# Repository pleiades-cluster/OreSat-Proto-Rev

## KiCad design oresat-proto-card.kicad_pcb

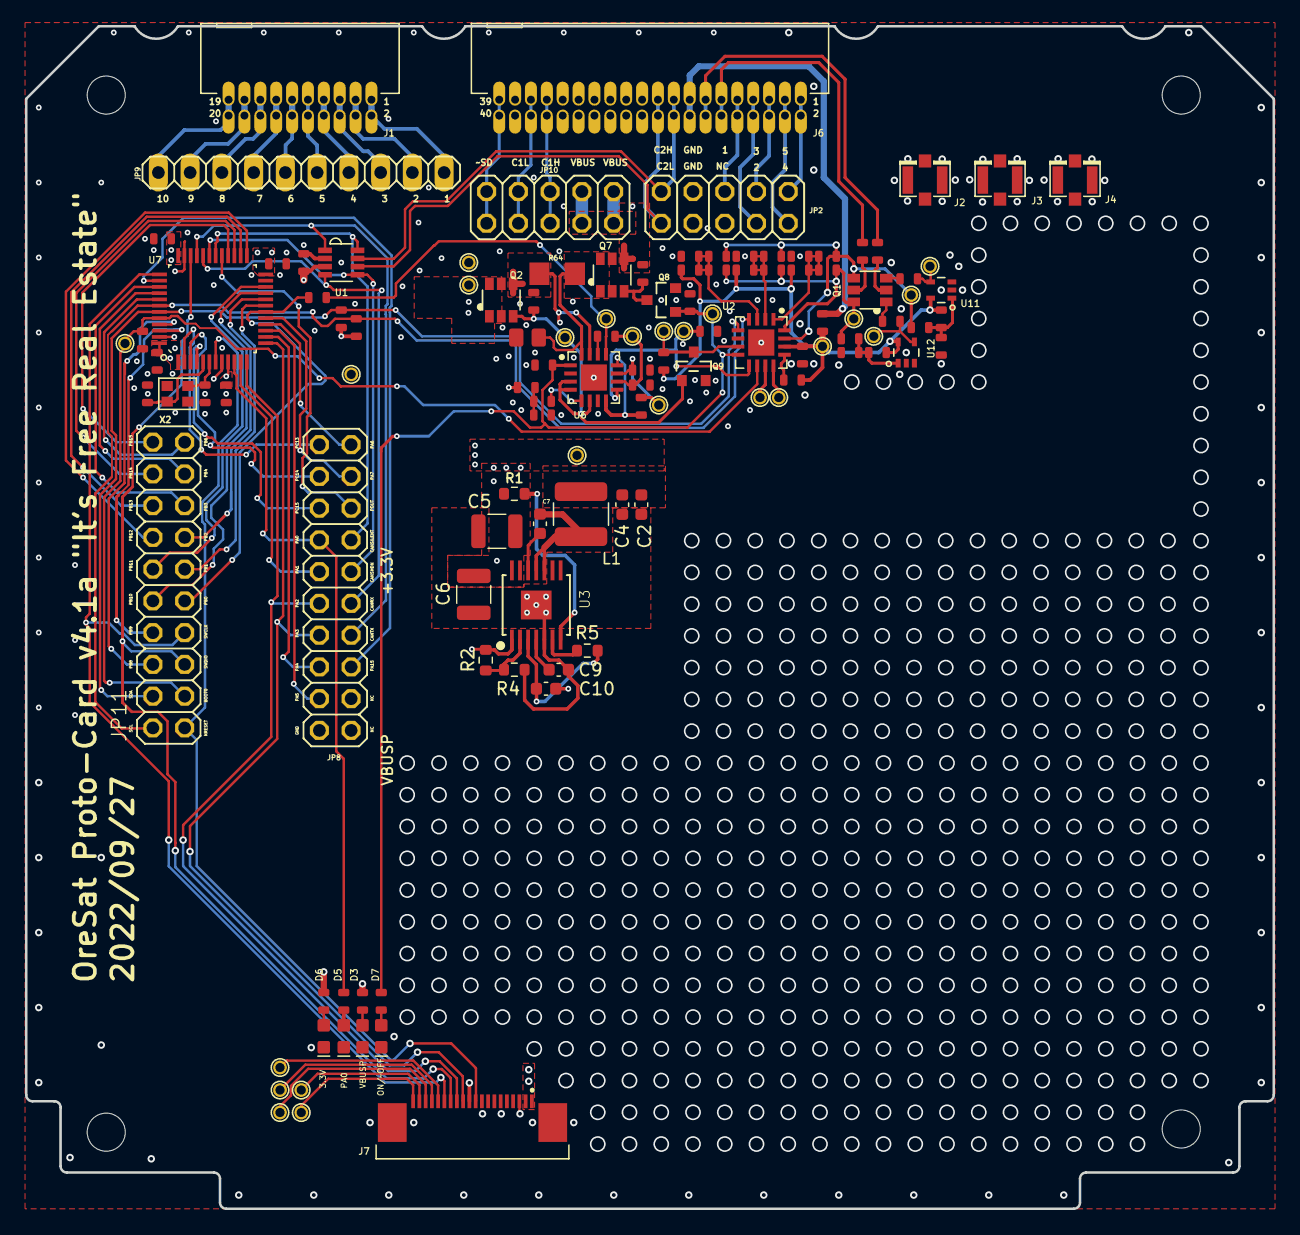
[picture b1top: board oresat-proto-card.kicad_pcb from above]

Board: 4 copper layers, 99.8 x 94.6 mm, 121 parts (0 on the bottom side), 113 nets.

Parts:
C1: CL21B106KOQNNNG; .0805-B-NOSILK
C2, C4: 22uF; C_0603_1608Metric
C3: C0603C104K4PAC7867; .0603-C-NOSILK
C5, C6: 100uF; C_1210_3225Metric
C7: 0.1uF; C_0603_1608Metric
C8: 1u; .0603-C-NOSILK
C9: 3.3nF; C_0603_1608Metric
C10: 1uF; C_0603_1608Metric
C13, C14, C19, C20, C21: CL05B104KO5NNNC; .0603-C-NOSILK
C15, C18: CL05C200JB51PNC; .0603-C-NOSILK
C17, C22, C23: CC0603KRX5R7BB105; .0603-C-NOSILK
D3, D6: SML-E12M8WT86; LED-0603
D5, D7: IN-S63AT5A; LED-0603
H2, H3: STAND-OFFTIGHT; STAND-OFF-TIGHT
J1: TFM-110-01-L-D-RA; J-SAMTEC-TFM-110-X1-XXX-D-RA
J2, J3, J4: 1909763-1; U.FL
J6: TFM-120-01-L-D-RA; J-SAMTEC-TFM-120-X1-XXX-D-RA
J7: ORESAT-DEBUG-CONNECTOR-ALL; TE_2-1734592-0
JP2, JP10: 67997-410HLF; 2X05
JP8, JP11: 67996-420HLF; 2X10
JP9: 61302011121; 1X10
L1: 3.3uH; L_2141
Q1: DMP2240UDM; SOT23-6
Q2, Q7: DMP3050LVT-7; SOT23-6
Q8, Q9: PMV45EN2R; SOT23
R1, R2: 73.2K; R_0603_1608Metric
R3, R17, R76: ERA-3AEB272V; .0603-C-NOSILK
R4: 22.1K; R_0603_1608Metric
R5: 100K; R_0603_1608Metric
R24: RC0603FR-0710RL; .0603-C-NOSILK
R39, R40, R45, R46, R52, R53, R54, R55, R56, R57, R58, R59, R67, R69, R71, R72: RC1005F6653CS; .0603-C-NOSILK
R47, R49: RC0402FR-0710KL; .0603-C-NOSILK
R48, R50, R51: CRGCQ0402F2K7; .0603-C-NOSILK
R60, R80: RC0603FR-07100RL; .0603-C-NOSILK
R61, R62, R63, R65, R70, R73, R77, R81: RNCP0603FTD10K0; .0603-C-NOSILK
R64: CSR1206FTR100; R1206
R66, R68: RC0603JR-070RL; .0603-C-NOSILK
R78, R82: CRGCQ0603F330K; .0603-C-NOSILK
R79, R83: RC0603FR-071ML; .0603-C-NOSILK
TP2, TP4, TP15, TP21, TP23, TP24, TP25, TP26, TP27, TP28, TP29, TP30, TP31, TP32, TP33, TP34, TP35, TP36, TP37, TP38, TP39, TP40, TP41, TP42: TEST-POINT-LARGE-SQUARE; 1X01
U1: TCAN330GDCNT; SOT23-8_TI-DCN
U2: MAX7310ATE; QFN65P400X400X80-17T210
U3: TPS54226PWPRPWP14_2P31X2P46-L; PWP14_2P31X2P46-L
U6: MAX4211FETE; QFN65P400X400X80-17T210
U7: STM32F042K6T7; STM32F091C
U11, U12: MIC842LYC5; SC70-5
X2: ECS-160-10-36Q-ES-TR; CRYSTAL_2.5X2

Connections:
3.3V: C2.2, C4.2, C13.2, C14.2, C19.2, C20.2, C21.2, J7.11 (VTARGET), L1.2, R2.2, R17.2, R50.2, R51.2, TP34.1, U1.3 (VCC), U3.1 (VO), U7.1 (VBAT), U7.9 (VDDA), U7.24 (VDD), U7.36 (VDDIO2), U7.48 (VDD)
/Connectors/AUX-1: J1.1, J1.2, JP9.1
/Connectors/AUX-2: J1.3, J1.4, JP9.2
/Connectors/AUX-3: J1.5, J1.6, JP9.3
/Connectors/AUX-4: J1.7, J1.8, JP9.4
/Connectors/AUX-5: J1.9, J1.10, JP9.5
/Connectors/AUX-6: J1.11, J1.12, JP9.6
/Connectors/AUX-7: J1.13, J1.14, JP9.7
/Connectors/AUX-8: J1.15, J1.16, JP9.8
/Connectors/AUX-9: J1.17, J1.18, JP9.9
/Connectors/AUX_~SHUTDOWN: J1.19, J1.20, JP9.10
/Connectors/CAN1_H: J6.33, J6.34, JP10.5, JP10.6
/Connectors/CAN1_L: J6.35, J6.36, JP10.7, JP10.8
/Connectors/SPARE1: J6.9, J6.10, JP2.5
/Connectors/SPARE2: J6.7, J6.8, JP2.4
/Connectors/SPARE3: J6.5, J6.6, JP2.3
/Connectors/SPARE4: J6.3, J6.4, JP2.2
/Connectors/SPARE5: J6.1, J6.2, JP2.1
/Connectors/~SD: J6.39, J6.40, JP10.9, JP10.10
/Microcontroller/CAN_RX: JP8.12, U1.4 (RXD), U7.32 (PA11)
/Microcontroller/CAN_SHDN: JP8.10, U1.5 (SHDN), U7.31 (PA10)
/Microcontroller/CAN_TX: JP8.14, U1.1 (TXD), U7.33 (PA12)
/Microcontroller/NRESET: J7.10 (NRST), JP11.1, U7.7 (NRST)
/Microcontroller/PA0: JP8.7, R48.2, U7.10 (PA0)
/Microcontroller/PA1: JP8.9, U7.11 (PA1)
/Microcontroller/PA2/USART2_TX: J7.13 (CARD-TX), JP8.11, U7.12 (PA2)
/Microcontroller/PA3/USART2_RX: J7.12 (CARD-RX), JP8.13, U7.13 (PA3)
/Microcontroller/PA4: JP8.15, U7.14 (PA4)
/Microcontroller/PA5/SPI1_SCK: JP8.17, U7.15 (PA5)
/Microcontroller/PA6/SPI1_MISO: JP8.2, U7.16 (PA6)
/Microcontroller/PA7/SPI1_MOSI: JP8.4, U7.17 (PA7)
/Microcontroller/PA8: JP8.6, U7.29 (PA8)
/Microcontroller/PA9/CAN_SILENT: JP8.8, U1.8 (S), U7.30 (PA9)
/Microcontroller/PA15: JP8.16, U7.38 (PA15)
/Microcontroller/PB0/POUTPROT: JP11.9, R49.2, U7.18 (PB0)
/Microcontroller/PB1: JP11.11, U7.19 (PB1)
/Microcontroller/PB2: JP11.13, U7.20 (PB2)
/Microcontroller/PB3: JP11.15, U7.39 (PB3)
/Microcontroller/PB4: JP11.17, U7.40 (PB4)
/Microcontroller/PB5: JP11.19, U7.41 (PB5)
/Microcontroller/PB8: JP11.6, U7.45 (PB8)
/Microcontroller/PB9: JP11.8, U7.46 (PB9)
/Microcontroller/PB10: JP11.10, U7.21 (PB10)
/Microcontroller/PB11: JP11.12, U7.22 (PB11)
/Microcontroller/PB12: JP11.14, U7.25 (PB12)
/Microcontroller/PB13: JP11.16, U7.26 (PB13)
/Microcontroller/PB14: JP11.18, U7.27 (PB14)
/Microcontroller/PB15: JP11.20, U7.28 (PB15)
/Microcontroller/PC13: JP8.1, U7.2 (PC13)
/Microcontroller/PC14: JP8.3, U7.3 (PC14-OSC32_IN)
/Microcontroller/PC15: JP8.5, U7.4 (PC15-OSC32_OUT)
/Microcontroller/SWCLK: J7.15 (SWCLK), JP11.7, U7.37 (PA14-SWCLK)
/Microcontroller/SWDIO: J7.14 (SWDIO), JP11.5, U7.34 (PA13-SWDIO)
/Power/AD0: R39.1, R40.2, R45.2, R46.1, U2.1 (AD0)
/Power/AD1: R52.1, R53.2, R54.2, R55.1, U2.2 (AD1)
/Power/AD2: R56.1, R57.2, R58.2, R59.1, U2.3 (AD2)
/Power/CB-RESET: R65.2, TP23.1, U2.9 (IO4), U6.9 (CIN2-)
/Power/CB_CTRL: Q2.3, Q9.1 (G), R70.1, TP39.1, U6.3 (LE), U6.4 (COUT1), U6.6 (COUT2)
/Power/ON/~OFF: C17.1, Q8.1 (G), R63.2, R76.2, TP21.1, U2.8 (IO3), U6.1 (VCC)
/Power/PEN-SCL-FILT: Q1.4 (D), R40.1, R53.1, R57.1, R82.2, TP37.1, U2.15 (SCL)
/Power/PEN-SDA-FILT: Q1.6 (D), R46.2, R55.2, R59.2, R78.2, TP38.1, U2.16 (SDA)
/Power/~FAULT: Q9.3 (D), R73.1, TP24.1, U2.7 (IO2)
BOOT0: JP11.3, R47.2, TP25.1, U2.10 (IO5), U7.44 (PF11-BOOT0)
CAN2_H: J6.17, J6.18, JP2.9, U1.7 (CANH)
CAN2_L: J6.19, J6.20, JP2.10, U1.6 (CANL)
GND: C1.2, C2.1, C3.1, C4.1, C5.2, C6.2, C9.2, C10.2, C13.1, C14.1, C15.2, C17.2, C18.2, C19.1, C20.1, C21.1, C22.2, C23.2, D3.C, D5.C, D6.C, D7.C, J2.1 (GND), J2.2 (GND), J3.1 (GND), J3.2 (GND), J4.1 (GND), J4.2 (GND), J6.27, J6.28, J6.29, J6.30, J6.31, J6.32, J7.3 (GND), J7.6 (GND), J7.9 (GND), J7.PAD1 (PAD), J7.PAD2 (PAD), JP2.7, JP2.8, JP8.19, Q8.2 (S), Q9.2 (S), R4.1, R45.1, R47.1, R54.1, R58.1, R63.1, R65.1, R67.1, R69.1, R71.1, U1.2 (GND), U2.6 (GND), U2.EPAD (GND), U3.5 (GND), U3.8 (PGND1), U3.9 (PGND2), U3.15 (EPAD), U6.7 (GND), U6.EPAD (GND), U7.8 (VSSA), U7.23 (VSS), U7.35 (VSS), U7.47 (VSS), U11.2 (GND), U12.2 (GND), X2.2 (SHIELD), X2.4 (SHIELD)
unnamed: C1.1, Q7.1 (G), Q7.2, Q7.5 (S), Q7.6 (D), R64.1, U6.16 (RS+)
unnamed: C7.1, L1.1, U3.10 (SW1), U3.11 (SW2)
unnamed: C7.2, U3.12 (VBST)
unnamed: C8.1, R71.2, R72.2
unnamed: C9.1, U3.4 (SS)
unnamed: C10.1, R5.2, U3.3 (VREG5)
unnamed: C15.1, U7.6 (PF1-OSC_OUT), X2.3 (2)
unnamed: C18.1, U7.5 (PF0-OSC_IN), X2.1
unnamed: C22.1, R78.1, R79.1, U12.1 (INP)
unnamed: C23.1, R82.1, R83.1, U11.1 (INP)
unnamed: D3.A, R3.1
unnamed: D5.A, R48.1
unnamed: D6.A, R17.1
unnamed: D7.A, R76.1
unnamed: J7.16 (SWO), TP30.1
unnamed: J7.17 (DEBUG-0), TP26.1
unnamed: J7.18 (DEBUG-1), TP27.1
unnamed: J7.19 (DEBUG-2), TP28.1
unnamed: J7.20 (DEBUG-3), TP29.1
unnamed: Q1.1 (G), R77.2
unnamed: Q1.2 (S), R80.2
unnamed: Q1.3 (G), R81.2
unnamed: Q1.5 (S), R60.2
unnamed: Q2.4, R64.2, R70.2, U6.15 (RS-)
unnamed: Q7.3, Q8.3 (D), R62.1
unnamed: R1.2, U3.7 (EN)
unnamed: R2.1, R4.2, U3.2 (VFB)
unnamed: R5.1, U3.6 (PG)
unnamed: R61.1, U2.13 (~RESET)
unnamed: R66.1, R67.2, TP15.1, U6.10 (CIN1+)
unnamed: R66.2, U6.14 (IOUT)
unnamed: R68.1, R69.2, TP4.1, U6.11 (CIN1-)
unnamed: R68.2, U6.8 (CIN2+), U6.12 (REF)
unnamed: R72.1, U6.5 (INHIBIT)
unnamed: R77.1, TP41.1, U12.4 (OUT)
unnamed: R81.1, TP42.1, U11.4 (OUT)
unnamed: TP36.1, U2.12 (IO7)
unnamed: TP40.1, U2.11 (IO6)
OPD_PWR: J6.15, J6.16, R24.1
OPD_SCL: J6.13, J6.14, R80.1
OPD_SDA: J6.11, J6.12, R60.1
PB6/SCL: JP11.2, R50.1, U2.4 (IO0), U7.42 (PB6)
PB7/SDA: JP11.4, R51.1, U2.5 (IO1), U7.43 (PB7)
POUT: R49.1, TP2.1, U6.13 (POUT)
VBUS: J6.21, J6.22, J6.23, J6.24, J6.25, J6.26, JP10.1, JP10.2, JP10.3, JP10.4, Q7.4, R62.2
VBUSP: C5.1, C6.1, C8.2, J7.1 (VBUSP), J7.2 (VBUSP), Q2.1 (G), Q2.2, Q2.5 (S), Q2.6 (D), R1.1, R3.2, TP31.1, U3.13 (VIN), U3.14 (VCC)
VPD: C3.2, R24.2, R39.2, R52.2, R56.2, R61.2, R73.2, R79.2, R83.2, TP35.1, U2.14 (V+), U11.5 (VDD), U12.5 (VDD)

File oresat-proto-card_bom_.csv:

Component,Description,Part,References,Value,Footprint,Quantity Per PCB,Datasheet,Generic,Manufacturer_Name,Manufacturer_Part_Number,Flight,Proto,Notes,Manufactuer_Part_Number
1,,C-EU0603-C-NOSILK,C15 C18,20p,.0603-C-NOSILK,2,,,,,,,,
2,,3.3NF-0603-100V-10%,C9,3.3nF,C_0603_1608Metric,1,,,,,,,,
3,,C-EU0603-C-NOSILK,C3 C13 C14 C19 C20 C21,100n,.0603-C-NOSILK,6,,,,,,,,
4,,1.0UF-0603-16V-10%,C7,0.1uF,C_0603_1608Metric,1,,,,,,,,
5,,1.0UF-0603-16V-10%,C10,1uF,C_0603_1608Metric,1,,,,,,,,
6,,C-EU0603-C-NOSILK,C8 C17 C22 C23,1u,.0603-C-NOSILK,4,,,,,,,,
7,,C-EU0805-B-NOSILK,C1,10u,.0805-B-NOSILK,1,,,,,,,,
8,,22UF-0805-6.3V-20%,C2 C4,22uF,C_0603_1608Metric,2,,,,,,,,
9,,22UF-1210-16V-20%,C5 C6,100uF,C_1210_3225Metric,2,,,,,,,,
10,,LED-GREEN0603,D5 D7,AMBER,LED-0603,2,,,,,,,,
11,,LED-GREEN0603,D3 D6,GREEN,LED-0603,2,,,,,,,,
12,,STAND-OFFTIGHT,H2 H3,STAND-OFFTIGHT,STAND-OFF-TIGHT,2,,,,,,,,
13,,J-SAMTEC-TFM-110-X1-XXX-D-RA,J1,J-SAMTEC-TFM-110-X1-XXX-D-RA,J-SAMTEC-TFM-110-X1-XXX-D-RA,1,,,,,,,,
14,,J-SAMTEC-TFM-120-X1-XXX-D-RA,J6,J-SAMTEC-TFM-120-X1-XXX-D-RA,J-SAMTEC-TFM-120-X1-XXX-D-RA,1,,N,Samtech,TFM-120-01-L-D-RA,,,,
15,,ORESAT-DEBUG-CONNECTOR-ALL,J7,ORESAT-DEBUG-CONNECTOR-ALL,TE_2-1734592-0,1,,,TE Connectivity AMP Connectors,2-1734592-0,,,,
16,,U.FL2PIN,J2 J3 J4,U.FL,U.FL,3,,,,,,,,
17,,PINHD-1X10,JP9,PINHD-1X10,1X10,1,,,,,,,,
18,,PINHD-2X10,JP8 JP11,PINHD-2X10,2X10,2,,,,,,,,
19,,PINHD-2X5,JP2 JP10,PINHD-2X5,2X05,2,,,,,,,,
20,Inductor,L,L1,3.3uH,L_2141,1,https://datasheet.lcsc.com/lcsc/2009171412_TAI-TECH-HPC5040N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,,TAI-TECH,HPC5040NF-3R3MTH,SPM5030T-3R3M-HZ,HPC5040NF-3R3MTH,,
21,,MOSFET-PCH-SOT23-6,Q2 Q7,MOSFET-PCH-SOT23-6,SOT23-6,2,https://www.diodes.com/assets/Datasheets/DMP3050LVT.pdf,N,Diodes Incorporated,DMP3050LVT-7,,,Make sure to verify footprint,
22,,PMV45EN,Q8 Q9,PMV45EN,SOT23,2,https://ww1.microchip.com/downloads/aemDocuments/documents/O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,N,Microchip Technology,PMV45EN2R,,,,
23,,MOSFET-PCH-SOT23-6,Q1,~,SOT23-6,1,https://www.diodes.com/assets/Datasheets/ds31197.pdf,N,Diodes Incorporated,DMP2240UDM-7,,,,
24,,R-US_0603-C-NOSILK,R66 R68,0,.0603-C-NOSILK,2,,,,,,,,
25,,R-US_R1206,R64,100m,R1206,1,,,,,,,,
26,,R-US_0603-C-NOSILK,R24,10,.0603-C-NOSILK,1,,,,,,,,
27,,R-US_0603-C-NOSILK,R60 R80,100,.0603-C-NOSILK,2,,,,,,,,
28,,R-US_0603-C-NOSILK,R3 R17 R48 R76,2.7k,.0603-C-NOSILK,4,,,,,,,,
29,,R-US_0603-C-NOSILK,R50 R51,4.7k,.0603-C-NOSILK,2,,,,,,,,
30,,R-US_0603-C-NOSILK,R47 R49 R61 R62 R63 R65 R70 R72 R73,10k,.0603-C-NOSILK,9,,,,,,,,
31,,R-US_R0603,R4,22.1K,R_0603_1608Metric,1,,,,,,,,
32,,R-US_R0603,R1 R2,73.2K,R_0603_1608Metric,2,,,,,,,,
33,,R-US_R0603,R5,100K,R_0603_1608Metric,1,,,,,,,,
34,,R-US_0603-C-NOSILK,R71,100k,.0603-C-NOSILK,1,,,,,,,,
35,,R-US_0603-C-NOSILK,R78 R82,330k,.0603-C-NOSILK,2,,,,,,,,
36,,R-US_0603-C-NOSILK,R77 R81,665k,.0603-C-NOSILK,2,,,,,,,,
37,,R-US_0603-C-NOSILK,R79 R83,1M,.0603-C-NOSILK,2,,,,,,,,
38,,R-US_0603-C-NOSILK,R39 R40 R45 R46 R52 R53 R54 R55 R56 R57 R58 R59 R67 R69,NP,.0603-C-NOSILK,14,,,,,,,,
39,,MAX4211,U6,MAX4211FETE+,QFN65P400X400X80-17T210,1,https://datasheets.maximintegrated.com/en/ds/MAX4210-MAX4211.pdf,N,Maxim,MAX4211FETE+,,,,
40,,MAX7310,U2,MAX7310ATE,QFN65P400X400X80-17T210,1,https://datasheets.maximintegrated.com/en/ds/MAX7310.pdf,N,Maxim,MAX7310ATE+,,,,
41,,MIC842LYC5,U11 U12,MIC842LYC5,SC70-5,2,https://ww1.microchip.com/downloads/aemDocuments/documents/O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,N,Microchip Technology,MIC842LYC5-TR,,,,MIC842LYC5-TR
42,,STM32F091C,U7,STM32F091C,STM32F091C,1,https://www.st.com/content/ccc/resource/technical/document/d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,N,ST Microelectronics,STM32F091CCT6,,,,
43,,TCAN330,U1,TCAN330,SOT23-8_TI-DCN,1,,N,,TCAN330GDCNT,,,,
44,,TPS54226PWPRPWP14_2P31X2P46-L,U3,TPS54226PWPRPWP14_2P31X2P46-L,PWP14_2P31X2P46-L,1,https://www.ti.com/lit/gpn/tps54226,,Texas Instruments,TPS54226PWPR,TPS54226PWPR,TPS54226PWPR,,
45,,CRYSTAL-WITH-GND,X2,16MHZ-2.5x2mm,CRYSTAL_2.5X2,1,,Y,,ECS-160-10-36Q-ES-TR,,,,





Component Groups:,45
Component Count:,97
Fitted Components:,97
Number of PCBs:,1
Total components:,97
Schematic Version:,
Schematic Date:,
PCB Variant:,default
BoM Date:,10/12/2022 4:32:53 PM
Schematic Source:,oresat-proto-card.kicad_sch
KiCad Version:,Eeschema (6.0.7)

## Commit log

2022-09-28 Rev V0
2022-09-28 Update 1
2022-09-29 Update V0.1
    Quashing DRC errors left and right
2022-09-29 Update V0.3
    Quashed all the DRC errors! Probably pretty stable now.
2022-10-05 Updated card
2022-10-12 Update Zip
2022-10-12 Reverted All Changes to V0.3
2022-10-12 Return of the Holes
2022-10-12 V0.4 BOM Updates and Footprint Fixes
2022-10-12 Moved Some Holes
